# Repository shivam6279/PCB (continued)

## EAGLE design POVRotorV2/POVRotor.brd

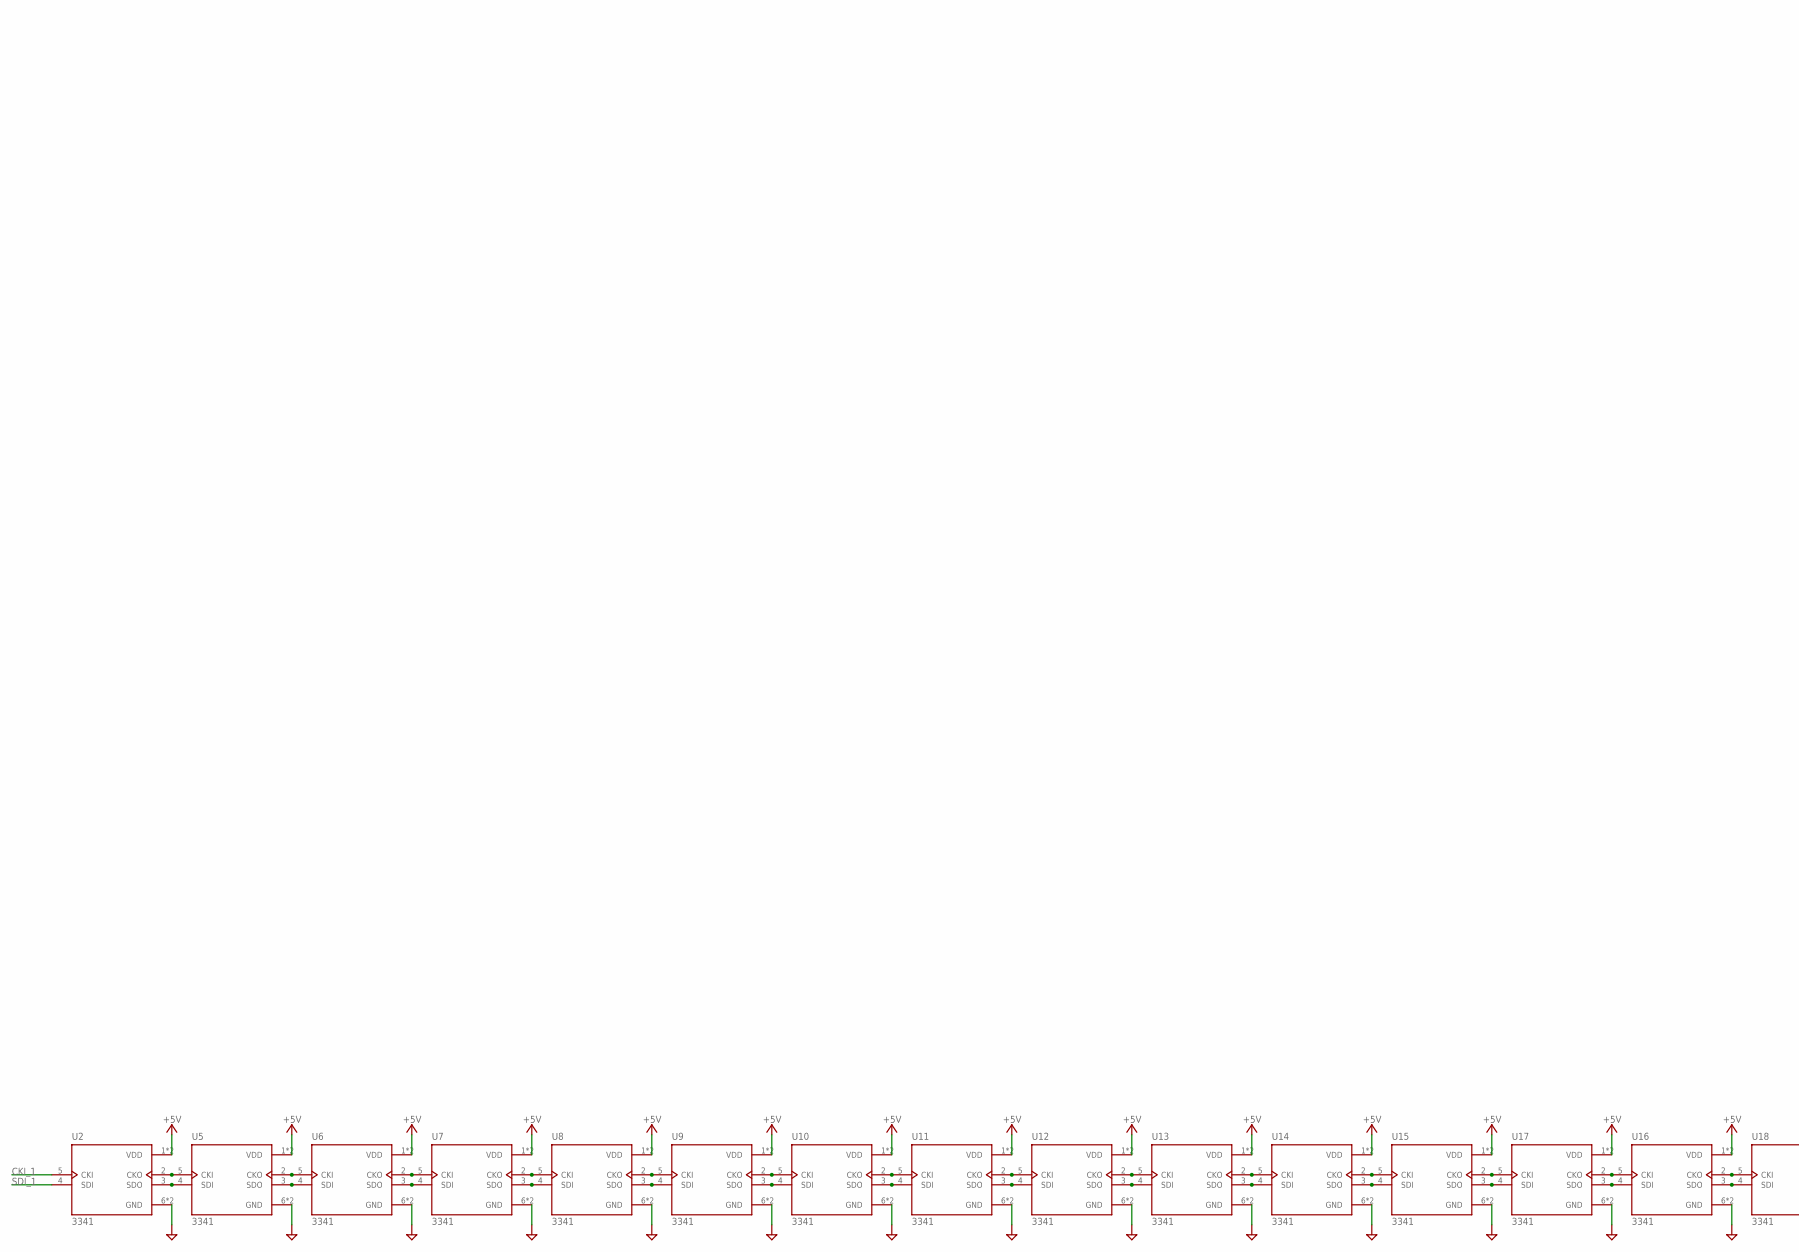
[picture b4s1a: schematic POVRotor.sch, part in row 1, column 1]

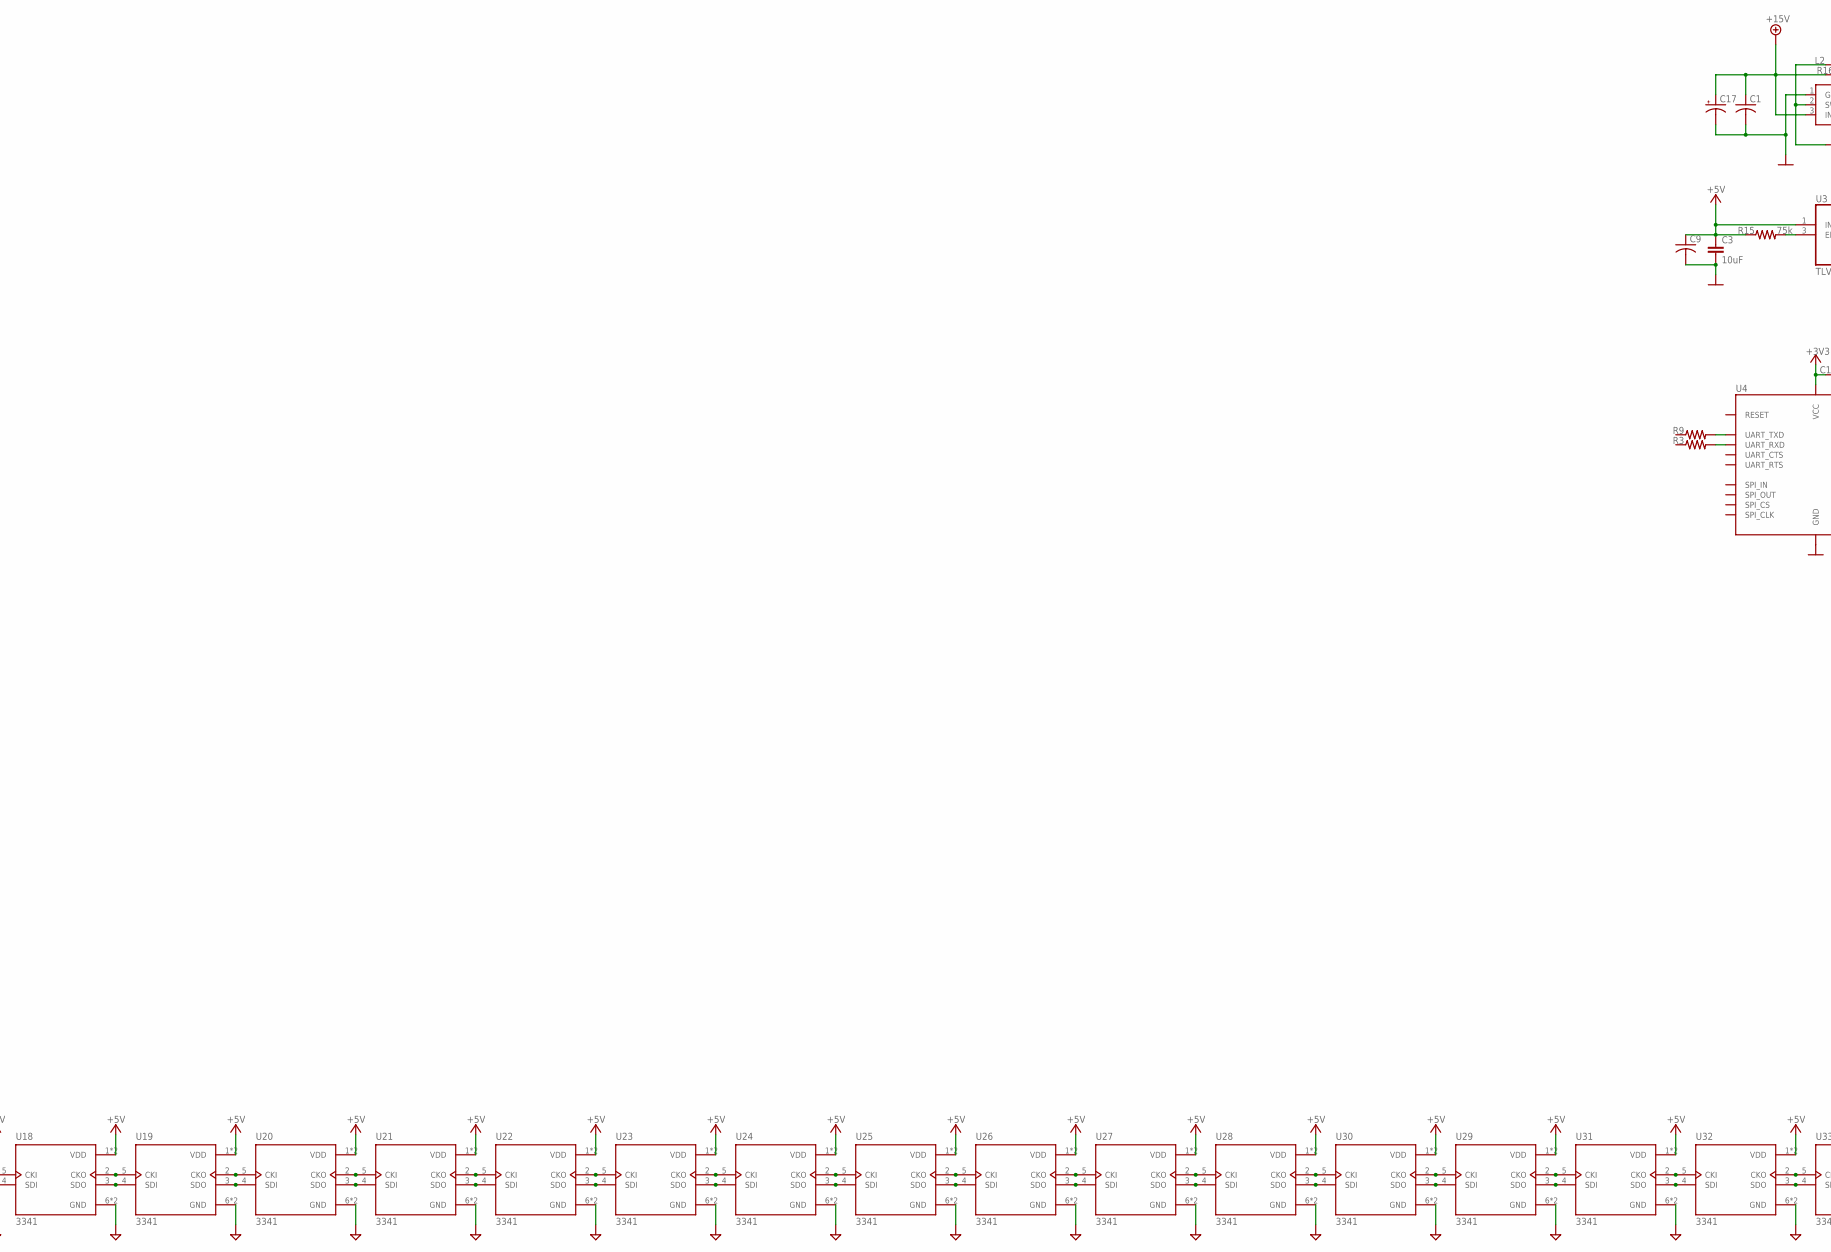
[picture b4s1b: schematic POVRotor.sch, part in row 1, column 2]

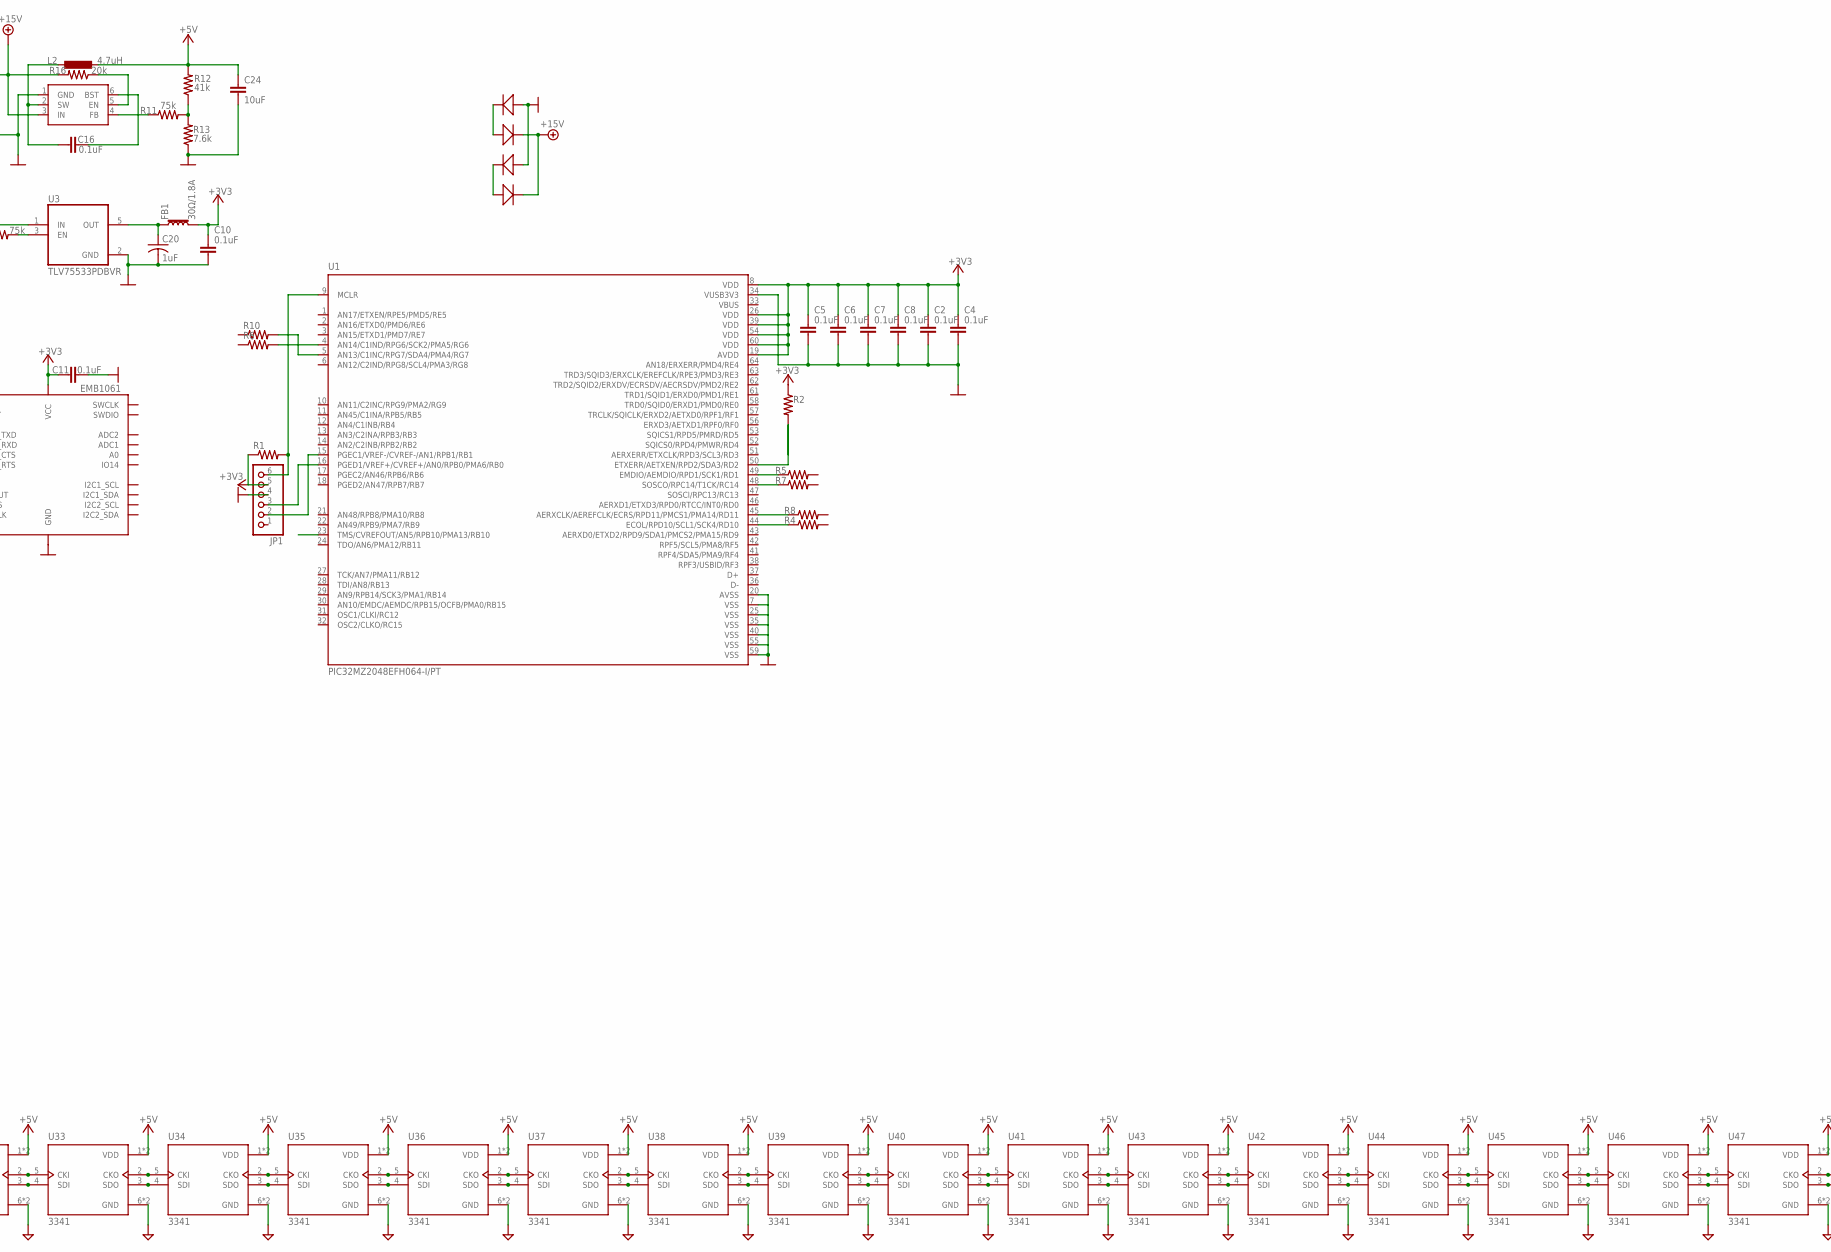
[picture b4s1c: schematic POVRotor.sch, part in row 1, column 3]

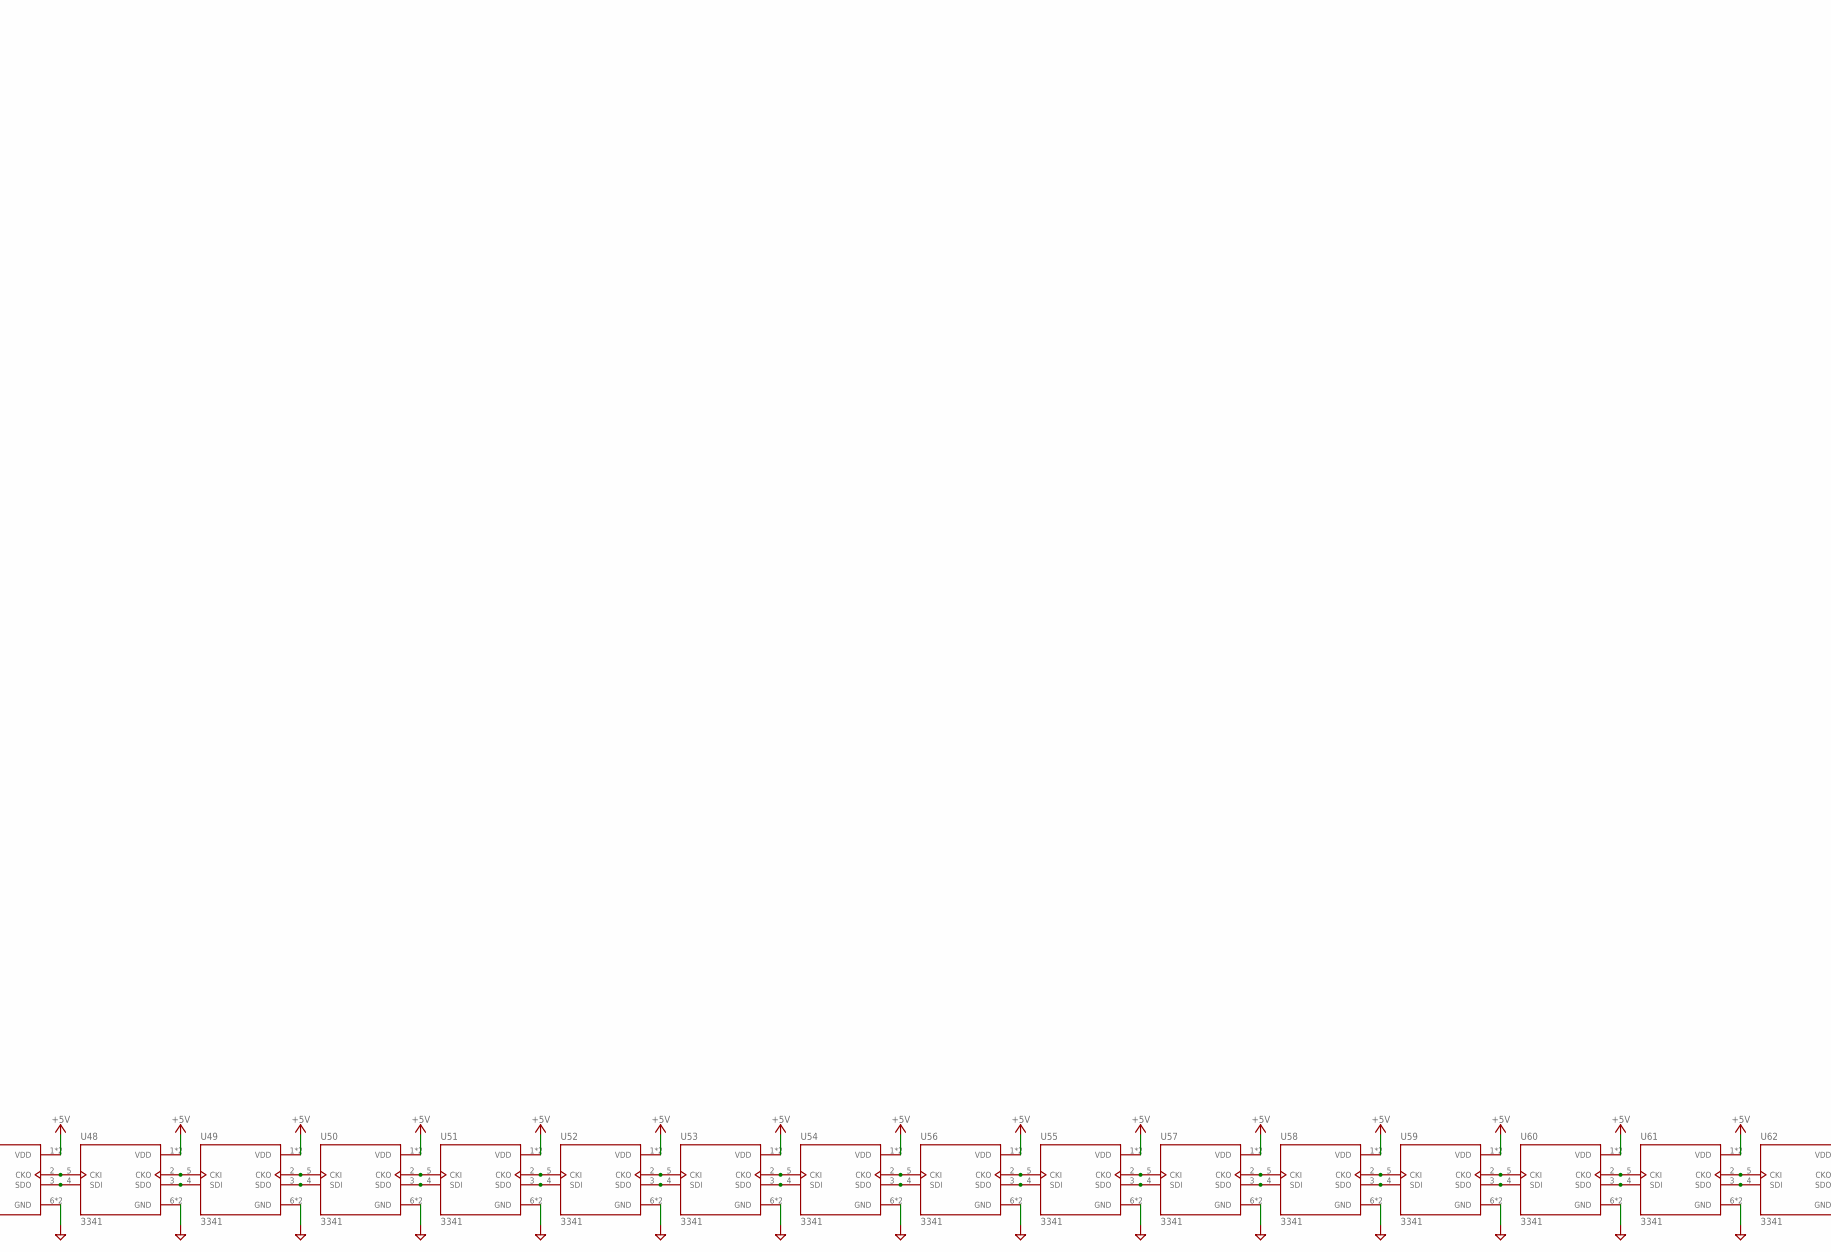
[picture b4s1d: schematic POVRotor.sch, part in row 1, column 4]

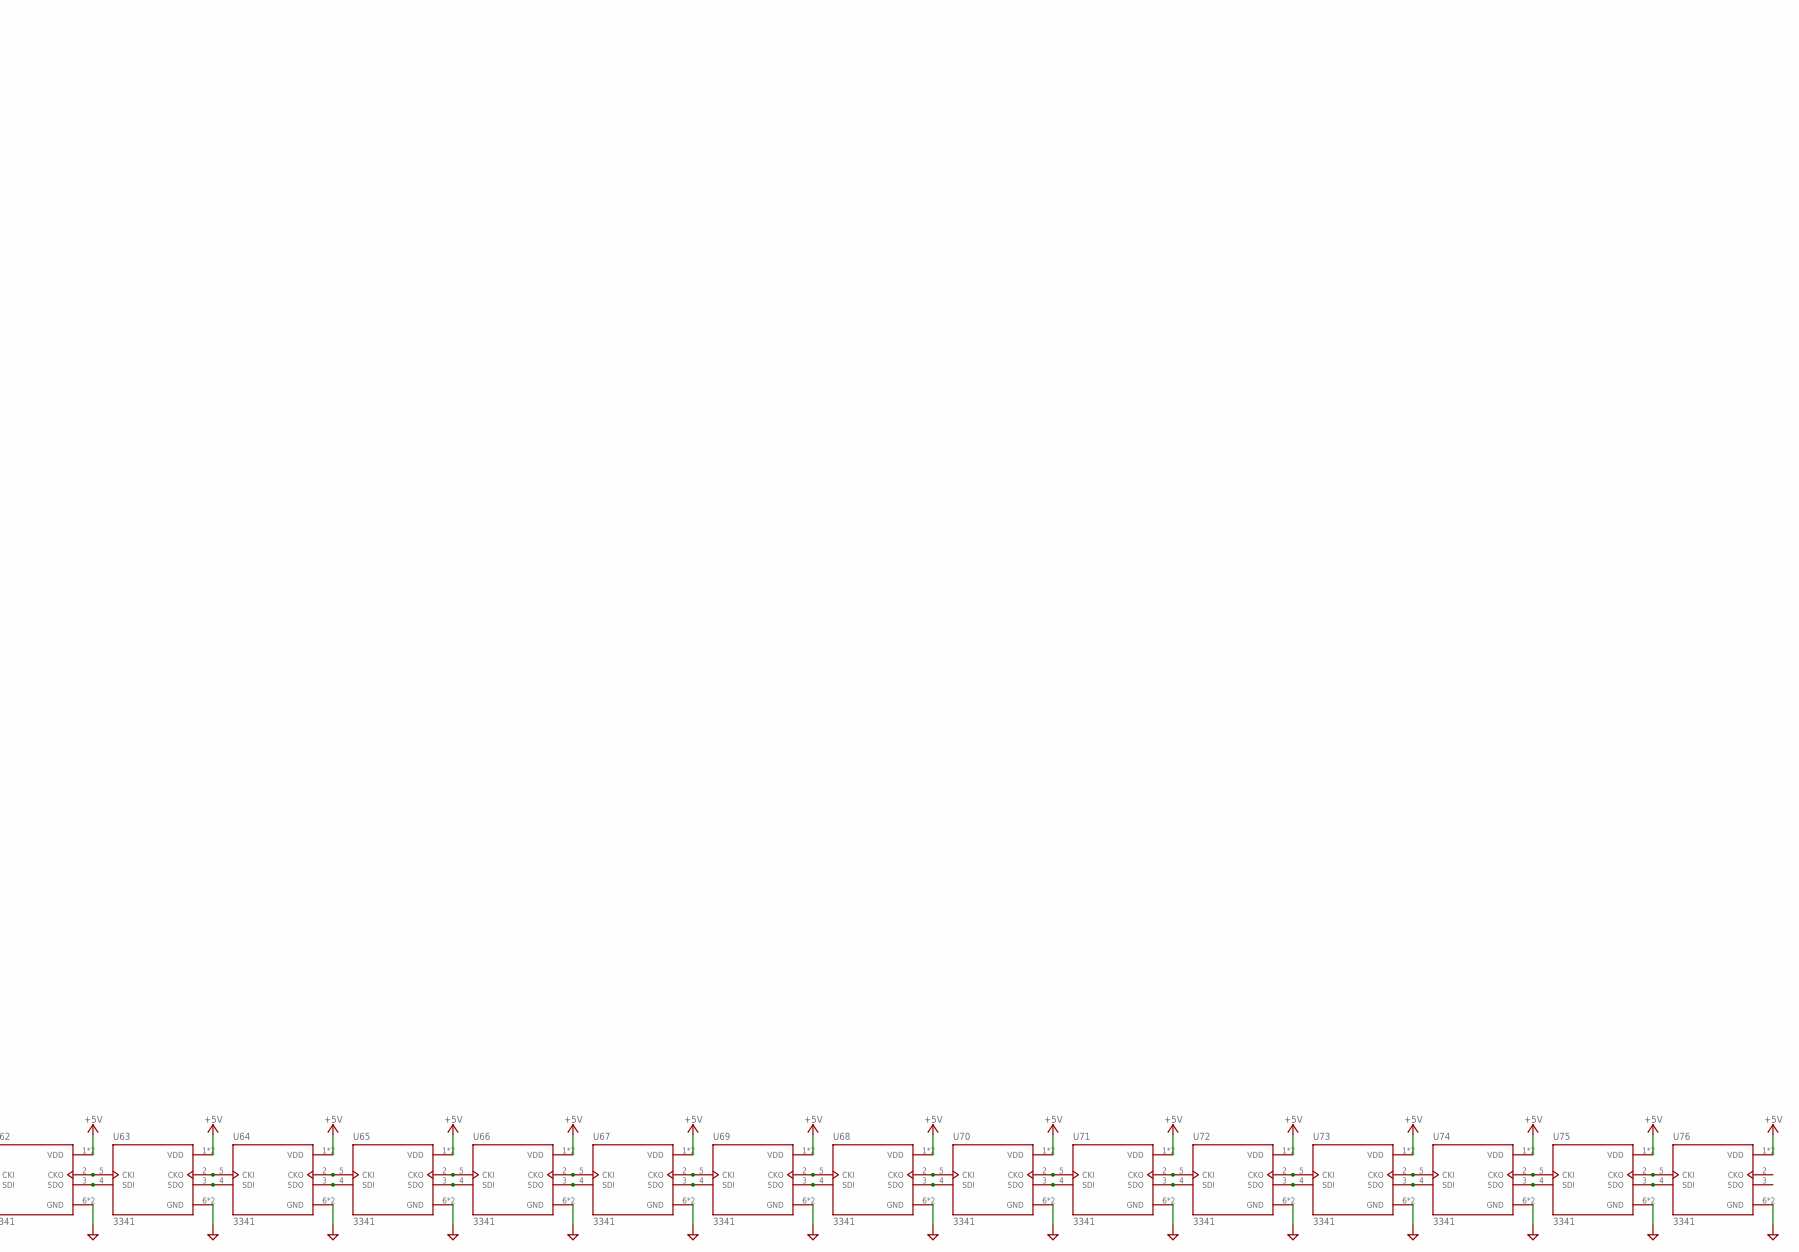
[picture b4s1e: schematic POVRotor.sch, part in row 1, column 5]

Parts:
C1, C9: C-USC0805; C0805
C2, C4, C5, C6, C7, C8, C10, C11, C16: 0.1uF; C0603
C3, C24: 10uF; C1206
C17: CPOL-USC/6032-28R; C/6032-28R
C20: 1uF; C0805
D2, D3, D4, D5: SMD-DIODE-SCHOTTKY-40V-3A(DO-214AB); DO-214AB
FB1: 30Ω/1.8A; 0603
JP1: PINHD-1X6/90; 1X06/90
L2: 4.7uH; L2825P
R1, R2, R3, R4, R5, R6, R7, R8, R9, R10: R-US_R0603; R0603
R11, R15: 75k; R0603
R12: 41k; R0603
R13: 7.6k; R0603
R16: 20k; R0603
U1: PIC32MZ2048EFH064-I/PT; QFP50P1200X1200X120-64N
U2, U5, U6, U7, U8, U9, U10, U11, U12, U13, U14, U15, U16, U17, U18, U19, U20, U21, U22, U23, U24, U25, U26, U27, U28, U29, U30, U31, U32, U33, U34, U35, U36, U37, U38, U39, U40, U41, U42, U43, U44, U45, U46, U47, U48, U49, U50, U51, U52, U53, U54, U55, U56, U57, U58, U59, U60, U61, U62, U63, U64, U65, U66, U67, U68, U69, U70, U71, U72, U73, U74, U75, U76: 3341; LED_3341
U3: TLV75533PDBVR; SOT95P280X145-5N
U4: EMB1061
U$74: AP65211A; SOT95P280X140-6N

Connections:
+5V: C3.1, C9.1, C24.1, L2.1, R12.2, R15.1, U2.1 (VDD), U2.8 (VDD), U3.1 (IN), U5.1 (VDD), U5.8 (VDD), U6.1 (VDD), U6.8 (VDD), U7.1 (VDD), U7.8 (VDD), U8.1 (VDD), U8.8 (VDD), U9.1 (VDD), U9.8 (VDD), U10.1 (VDD), U10.8 (VDD), U11.1 (VDD), U11.8 (VDD), U12.1 (VDD), U12.8 (VDD), U13.1 (VDD), U13.8 (VDD), U14.1 (VDD), U14.8 (VDD), U15.1 (VDD), U15.8 (VDD), U16.1 (VDD), U16.8 (VDD), U17.1 (VDD), U17.8 (VDD), U18.1 (VDD), U18.8 (VDD), U19.1 (VDD), U19.8 (VDD), U20.1 (VDD), U20.8 (VDD), U21.1 (VDD), U21.8 (VDD), U22.1 (VDD), U22.8 (VDD), U23.1 (VDD), U23.8 (VDD), U24.1 (VDD), U24.8 (VDD), U25.1 (VDD), U25.8 (VDD), U26.1 (VDD), U26.8 (VDD), U27.1 (VDD), U27.8 (VDD), U28.1 (VDD), U28.8 (VDD), U29.1 (VDD), U29.8 (VDD), U30.1 (VDD), U30.8 (VDD), U31.1 (VDD), U31.8 (VDD), U32.1 (VDD), U32.8 (VDD), U33.1 (VDD), U33.8 (VDD), U34.1 (VDD), U34.8 (VDD), U35.1 (VDD), U35.8 (VDD), U36.1 (VDD), U36.8 (VDD), U37.1 (VDD), U37.8 (VDD), U38.1 (VDD), U38.8 (VDD), U39.1 (VDD), U39.8 (VDD), U40.1 (VDD), U40.8 (VDD), U41.1 (VDD), U41.8 (VDD), U42.1 (VDD), U42.8 (VDD), U43.1 (VDD), U43.8 (VDD), U44.1 (VDD), U44.8 (VDD), U45.1 (VDD), U45.8 (VDD), U46.1 (VDD), U46.8 (VDD), U47.1 (VDD), U47.8 (VDD), U48.1 (VDD), U48.8 (VDD), U49.1 (VDD), U49.8 (VDD), U50.1 (VDD), U50.8 (VDD), U51.1 (VDD), U51.8 (VDD), U52.1 (VDD), U52.8 (VDD), U53.1 (VDD), U53.8 (VDD), U54.1 (VDD), U54.8 (VDD), U55.1 (VDD), U55.8 (VDD), U56.1 (VDD), U56.8 (VDD), U57.1 (VDD), U57.8 (VDD), U58.1 (VDD), U58.8 (VDD), U59.1 (VDD), U59.8 (VDD), U60.1 (VDD), U60.8 (VDD), U61.1 (VDD), U61.8 (VDD), U62.1 (VDD), U62.8 (VDD), U63.1 (VDD), U63.8 (VDD), U64.1 (VDD), U64.8 (VDD), U65.1 (VDD), U65.8 (VDD), U66.1 (VDD), U66.8 (VDD), U67.1 (VDD), U67.8 (VDD), U68.1 (VDD), U68.8 (VDD), U69.1 (VDD), U69.8 (VDD), U70.1 (VDD), U70.8 (VDD), U71.1 (VDD), U71.8 (VDD), U72.1 (VDD), U72.8 (VDD), U73.1 (VDD), U73.8 (VDD), U74.1 (VDD), U74.8 (VDD), U75.1 (VDD), U75.8 (VDD), U76.1 (VDD), U76.8 (VDD); also elsewhere on the board
+15V: C1.1, C17.+, D2.2 (-), D3.2 (-), R16.2, U$74.3 (IN)
BLE_RX: R3.2, U4.P$11 (UART_RXD)
BLE_TX: R9.2, U4.P$10 (UART_TXD)
CKI_1: R5.2, U2.5 (CKI)
GND: C1.2, C2.2, C3.2, C4.2, C5.2, C6.2, C7.2, C8.2, C9.2, C10.2, C11.2, C17.-, C20.2, C24.2, D4.1 (+), D5.1 (+), JP1.4, R13.1, U1.7 (VSS), U1.20 (AVSS), U1.25 (VSS), U1.34 (VUSB3V3), U1.35 (VSS), U1.40 (VSS), U1.55 (VSS), U1.59 (VSS), U2.6 (GND), U2.7 (GND), U3.2 (GND), U4.P$9 (GND), U4.P$22 (GND), U5.6 (GND), U5.7 (GND), U6.6 (GND), U6.7 (GND), U7.6 (GND), U7.7 (GND), U8.6 (GND), U8.7 (GND), U9.6 (GND), U9.7 (GND), U10.6 (GND), U10.7 (GND), U11.6 (GND), U11.7 (GND), U12.6 (GND), U12.7 (GND), U13.6 (GND), U13.7 (GND), U14.6 (GND), U14.7 (GND), U15.6 (GND), U15.7 (GND), U16.6 (GND), U16.7 (GND), U17.6 (GND), U17.7 (GND), U18.6 (GND), U18.7 (GND), U19.6 (GND), U19.7 (GND), U20.6 (GND), U20.7 (GND), U21.6 (GND), U21.7 (GND), U22.6 (GND), U22.7 (GND), U23.6 (GND), U23.7 (GND), U24.6 (GND), U24.7 (GND), U25.6 (GND), U25.7 (GND), U26.6 (GND), U26.7 (GND), U27.6 (GND), U27.7 (GND), U28.6 (GND), U28.7 (GND), U29.6 (GND), U29.7 (GND), U30.6 (GND), U30.7 (GND), U31.6 (GND), U31.7 (GND), U32.6 (GND), U32.7 (GND), U33.6 (GND), U33.7 (GND), U34.6 (GND), U34.7 (GND), U35.6 (GND), U35.7 (GND), U36.6 (GND), U36.7 (GND), U37.6 (GND), U37.7 (GND), U38.6 (GND), U38.7 (GND), U39.6 (GND), U39.7 (GND), U40.6 (GND), U40.7 (GND), U41.6 (GND), U41.7 (GND), U42.6 (GND), U42.7 (GND), U43.6 (GND), U43.7 (GND), U44.6 (GND), U44.7 (GND), U45.6 (GND), U45.7 (GND), U46.6 (GND), U46.7 (GND), U47.6 (GND), U47.7 (GND), U48.6 (GND), U48.7 (GND), U49.6 (GND), U49.7 (GND), U50.6 (GND), U50.7 (GND), U51.6 (GND), U51.7 (GND), U52.6 (GND), U52.7 (GND), U53.6 (GND), U53.7 (GND), U54.6 (GND), U54.7 (GND), U55.6 (GND), U55.7 (GND), U56.6 (GND), U56.7 (GND), U57.6 (GND), U57.7 (GND), U58.6 (GND), U58.7 (GND), U59.6 (GND), U59.7 (GND), U60.6 (GND), U60.7 (GND), U61.6 (GND), U61.7 (GND), U62.6 (GND), U62.7 (GND), U63.6 (GND), U63.7 (GND), U64.6 (GND), U64.7 (GND), U65.6 (GND), U65.7 (GND), U66.6 (GND), U66.7 (GND), U67.6 (GND), U67.7 (GND), U68.6 (GND), U68.7 (GND), U69.6 (GND), U69.7 (GND), U70.6 (GND), U70.7 (GND), U71.6 (GND), U71.7 (GND), U72.6 (GND), U72.7 (GND), U73.6 (GND), U73.7 (GND), U74.6 (GND), U74.7 (GND), U75.6 (GND), U75.7 (GND), U76.6 (GND), U76.7 (GND), U$74.1 (GND); also elsewhere on the board
unnamed: D2.1 (+), D5.2 (-)
unnamed: D3.1 (+), D4.2 (-)
unnamed: R15.2, U3.3 (EN)
unnamed: R9.1, U1.51 (AERXERR/ETXCLK/RPD3/SCL3/RD3)
unnamed: R4.2, U4.P$3 (RESET)
unnamed: R16.1, U$74.5 (EN)
unnamed: U5.2 (CKO), U6.5 (CKI)
unnamed: U5.3 (SDO), U6.4 (SDI)
unnamed: U2.2 (CKO), U5.5 (CKI)
unnamed: U2.3 (SDO), U5.4 (SDI)
unnamed: U6.2 (CKO), U7.5 (CKI)
unnamed: JP1.3, U1.16 (PGED1/VREF+/CVREF+/AN0/RPB0/PMA6/RB0)
unnamed: JP1.2, U1.15 (PGEC1/VREF-/CVREF-/AN1/RPB1/RB1)
unnamed: JP1.6, R1.2, U1.9 (MCLR)
unnamed: U26.2 (CKO), U27.5 (CKI)
unnamed: U6.3 (SDO), U7.4 (SDI)
unnamed: U7.2 (CKO), U8.5 (CKI)
unnamed: U7.3 (SDO), U8.4 (SDI)
unnamed: U8.2 (CKO), U9.5 (CKI)
unnamed: R6.1, R7.1, U1.48 (SOSCO/RPC14/T1CK/RC14)
unnamed: U8.3 (SDO), U9.4 (SDI)
unnamed: U9.2 (CKO), U10.5 (CKI)
unnamed: U9.3 (SDO), U10.4 (SDI)
unnamed: U10.2 (CKO), U11.5 (CKI)
unnamed: U10.3 (SDO), U11.4 (SDI)
unnamed: U11.2 (CKO), U12.5 (CKI)
unnamed: U11.3 (SDO), U12.4 (SDI)
unnamed: U12.2 (CKO), U13.5 (CKI)
unnamed: U12.3 (SDO), U13.4 (SDI)
unnamed: U13.2 (CKO), U14.5 (CKI)
unnamed: U13.3 (SDO), U14.4 (SDI)
unnamed: U14.2 (CKO), U15.5 (CKI)
unnamed: U14.3 (SDO), U15.4 (SDI)
unnamed: U15.2 (CKO), U17.5 (CKI)
unnamed: U15.3 (SDO), U17.4 (SDI)
unnamed: U16.5 (CKI), U17.2 (CKO)
unnamed: U16.4 (SDI), U17.3 (SDO)
unnamed: U18.2 (CKO), U19.5 (CKI)
unnamed: U18.3 (SDO), U19.4 (SDI)
unnamed: U16.2 (CKO), U18.5 (CKI)
unnamed: R5.1, U1.49 (EMDIO/AEMDIO/RPD1/SCK1/RD1)
unnamed: U16.3 (SDO), U18.4 (SDI)
unnamed: U19.2 (CKO), U20.5 (CKI)
unnamed: U19.3 (SDO), U20.4 (SDI)
unnamed: U20.2 (CKO), U21.5 (CKI)
unnamed: U20.3 (SDO), U21.4 (SDI)
unnamed: U21.2 (CKO), U22.5 (CKI)
unnamed: U21.3 (SDO), U22.4 (SDI)
unnamed: U22.2 (CKO), U23.5 (CKI)
unnamed: U22.3 (SDO), U23.4 (SDI)
unnamed: U23.2 (CKO), U24.5 (CKI)
unnamed: U23.3 (SDO), U24.4 (SDI)
unnamed: U24.2 (CKO), U25.5 (CKI)
unnamed: U24.3 (SDO), U25.4 (SDI)
unnamed: U25.2 (CKO), U26.5 (CKI)
unnamed: U25.3 (SDO), U26.4 (SDI)
unnamed: C20.1, FB1.1, U3.5 (OUT)
unnamed: U26.3 (SDO), U27.4 (SDI)
unnamed: U27.2 (CKO), U28.5 (CKI)
unnamed: U27.3 (SDO), U28.4 (SDI)
unnamed: U28.2 (CKO), U30.5 (CKI)
unnamed: U28.3 (SDO), U30.4 (SDI)
unnamed: U29.5 (CKI), U30.2 (CKO)
unnamed: U29.4 (SDI), U30.3 (SDO)
unnamed: U31.2 (CKO), U32.5 (CKI)
unnamed: U31.3 (SDO), U32.4 (SDI)
unnamed: U29.2 (CKO), U31.5 (CKI)
unnamed: U29.3 (SDO), U31.4 (SDI)
unnamed: U32.2 (CKO), U33.5 (CKI)
unnamed: U32.3 (SDO), U33.4 (SDI)
unnamed: U33.2 (CKO), U34.5 (CKI)
unnamed: U33.3 (SDO), U34.4 (SDI)
unnamed: U34.2 (CKO), U35.5 (CKI)
unnamed: U34.3 (SDO), U35.4 (SDI)
unnamed: U35.2 (CKO), U36.5 (CKI)
unnamed: U35.3 (SDO), U36.4 (SDI)
unnamed: U36.2 (CKO), U37.5 (CKI)
unnamed: U36.3 (SDO), U37.4 (SDI)
unnamed: U37.2 (CKO), U38.5 (CKI)
unnamed: U37.3 (SDO), U38.4 (SDI)
unnamed: U38.2 (CKO), U39.5 (CKI)
unnamed: U38.3 (SDO), U39.4 (SDI)
unnamed: U39.2 (CKO), U40.5 (CKI)
unnamed: U39.3 (SDO), U40.4 (SDI)
unnamed: U40.2 (CKO), U41.5 (CKI)
unnamed: U40.3 (SDO), U41.4 (SDI)
unnamed: U41.2 (CKO), U43.5 (CKI)
unnamed: U41.3 (SDO), U43.4 (SDI)
unnamed: U42.5 (CKI), U43.2 (CKO)
unnamed: U42.4 (SDI), U43.3 (SDO)
unnamed: U44.2 (CKO), U45.5 (CKI)
unnamed: U44.3 (SDO), U45.4 (SDI)
unnamed: U42.2 (CKO), U44.5 (CKI)
unnamed: U42.3 (SDO), U44.4 (SDI)
unnamed: U45.2 (CKO), U46.5 (CKI)
unnamed: U45.3 (SDO), U46.4 (SDI)
unnamed: U46.2 (CKO), U47.5 (CKI)
unnamed: U46.3 (SDO), U47.4 (SDI)
unnamed: U47.2 (CKO), U48.5 (CKI)
unnamed: U47.3 (SDO), U48.4 (SDI)
unnamed: U48.2 (CKO), U49.5 (CKI)
unnamed: U48.3 (SDO), U49.4 (SDI)
unnamed: U49.2 (CKO), U50.5 (CKI)
unnamed: U49.3 (SDO), U50.4 (SDI)
unnamed: U50.2 (CKO), U51.5 (CKI)
unnamed: U50.3 (SDO), U51.4 (SDI)
unnamed: U51.2 (CKO), U52.5 (CKI)
unnamed: U51.3 (SDO), U52.4 (SDI)
unnamed: U52.2 (CKO), U53.5 (CKI)
unnamed: U52.3 (SDO), U53.4 (SDI)
unnamed: U53.2 (CKO), U54.5 (CKI)
unnamed: U53.3 (SDO), U54.4 (SDI)
unnamed: U54.2 (CKO), U56.5 (CKI)
unnamed: U54.3 (SDO), U56.4 (SDI)
unnamed: U55.5 (CKI), U56.2 (CKO)
unnamed: U55.4 (SDI), U56.3 (SDO)
unnamed: U57.2 (CKO), U58.5 (CKI)
unnamed: U57.3 (SDO), U58.4 (SDI)
unnamed: U55.2 (CKO), U57.5 (CKI)
unnamed: U55.3 (SDO), U57.4 (SDI)
unnamed: U58.2 (CKO), U59.5 (CKI)
unnamed: C16.1, L2.2, U$74.2 (SW)
unnamed: C16.2, U$74.6 (BST)
unnamed: U58.3 (SDO), U59.4 (SDI)
unnamed: U59.2 (CKO), U60.5 (CKI)
unnamed: U59.3 (SDO), U60.4 (SDI)
unnamed: U60.2 (CKO), U61.5 (CKI)
unnamed: U60.3 (SDO), U61.4 (SDI)
unnamed: U61.2 (CKO), U62.5 (CKI)
unnamed: U61.3 (SDO), U62.4 (SDI)
unnamed: U62.2 (CKO), U63.5 (CKI)
unnamed: U62.3 (SDO), U63.4 (SDI)
unnamed: U63.2 (CKO), U64.5 (CKI)
unnamed: U63.3 (SDO), U64.4 (SDI)
unnamed: U64.2 (CKO), U65.5 (CKI)
unnamed: U64.3 (SDO), U65.4 (SDI)
unnamed: U65.2 (CKO), U66.5 (CKI)
unnamed: U65.3 (SDO), U66.4 (SDI)
unnamed: U66.2 (CKO), U67.5 (CKI)
unnamed: U66.3 (SDO), U67.4 (SDI)
unnamed: U67.2 (CKO), U69.5 (CKI)
unnamed: U67.3 (SDO), U69.4 (SDI)
unnamed: U68.5 (CKI), U69.2 (CKO)
unnamed: U68.4 (SDI), U69.3 (SDO)
unnamed: U70.2 (CKO), U71.5 (CKI)
unnamed: U70.3 (SDO), U71.4 (SDI)
unnamed: U68.2 (CKO), U70.5 (CKI)
unnamed: U68.3 (SDO), U70.4 (SDI)
unnamed: U71.2 (CKO), U72.5 (CKI)
unnamed: U71.3 (SDO), U72.4 (SDI)
unnamed: U72.2 (CKO), U73.5 (CKI)
unnamed: U72.3 (SDO), U73.4 (SDI)
unnamed: U73.2 (CKO), U74.5 (CKI)
unnamed: U73.3 (SDO), U74.4 (SDI)
unnamed: U74.2 (CKO), U75.5 (CKI)
unnamed: U74.3 (SDO), U75.4 (SDI)
unnamed: U75.2 (CKO), U76.5 (CKI)
unnamed: U75.3 (SDO), U76.4 (SDI)
unnamed: R11.1, U$74.4 (FB)
unnamed: R11.2, R12.1, R13.2
unnamed: R8.1, U1.45 (AERXCLK/AEREFCLK/ECRS/RPD11/PMCS1/PMA14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)
unnamed: R10.2, U1.5 (AN13/C1INC/RPG7/SDA4/PMA4/RG7)
VBUS: U1.33 (VBUS)

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
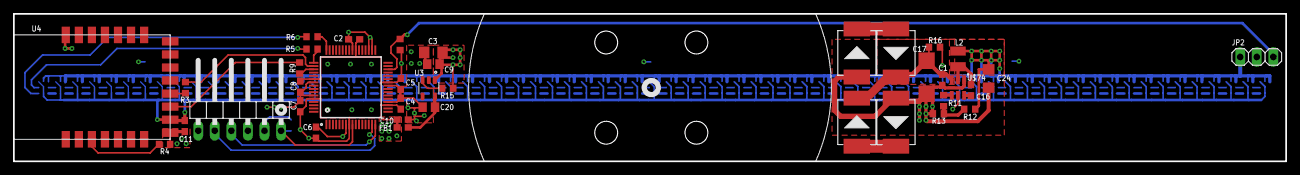
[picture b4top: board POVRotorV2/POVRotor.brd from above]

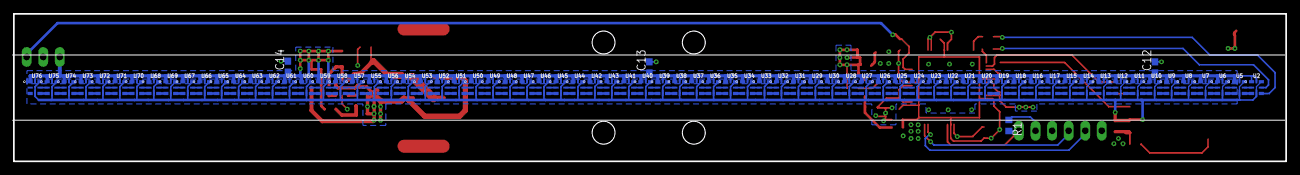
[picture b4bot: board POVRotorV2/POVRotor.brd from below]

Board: 4 copper layers, 195.0 x 22.6 mm, 115 parts (77 on the bottom side), 170 nets.

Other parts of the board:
C12, C13, C14: 0.1uF; C0603
JP2: 1X03

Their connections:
+5V: C12.1, C13.1, C14.1, JP2.1; also elsewhere on the board
GND: C12.2, C13.2, C14.2, JP2.2; also elsewhere on the board

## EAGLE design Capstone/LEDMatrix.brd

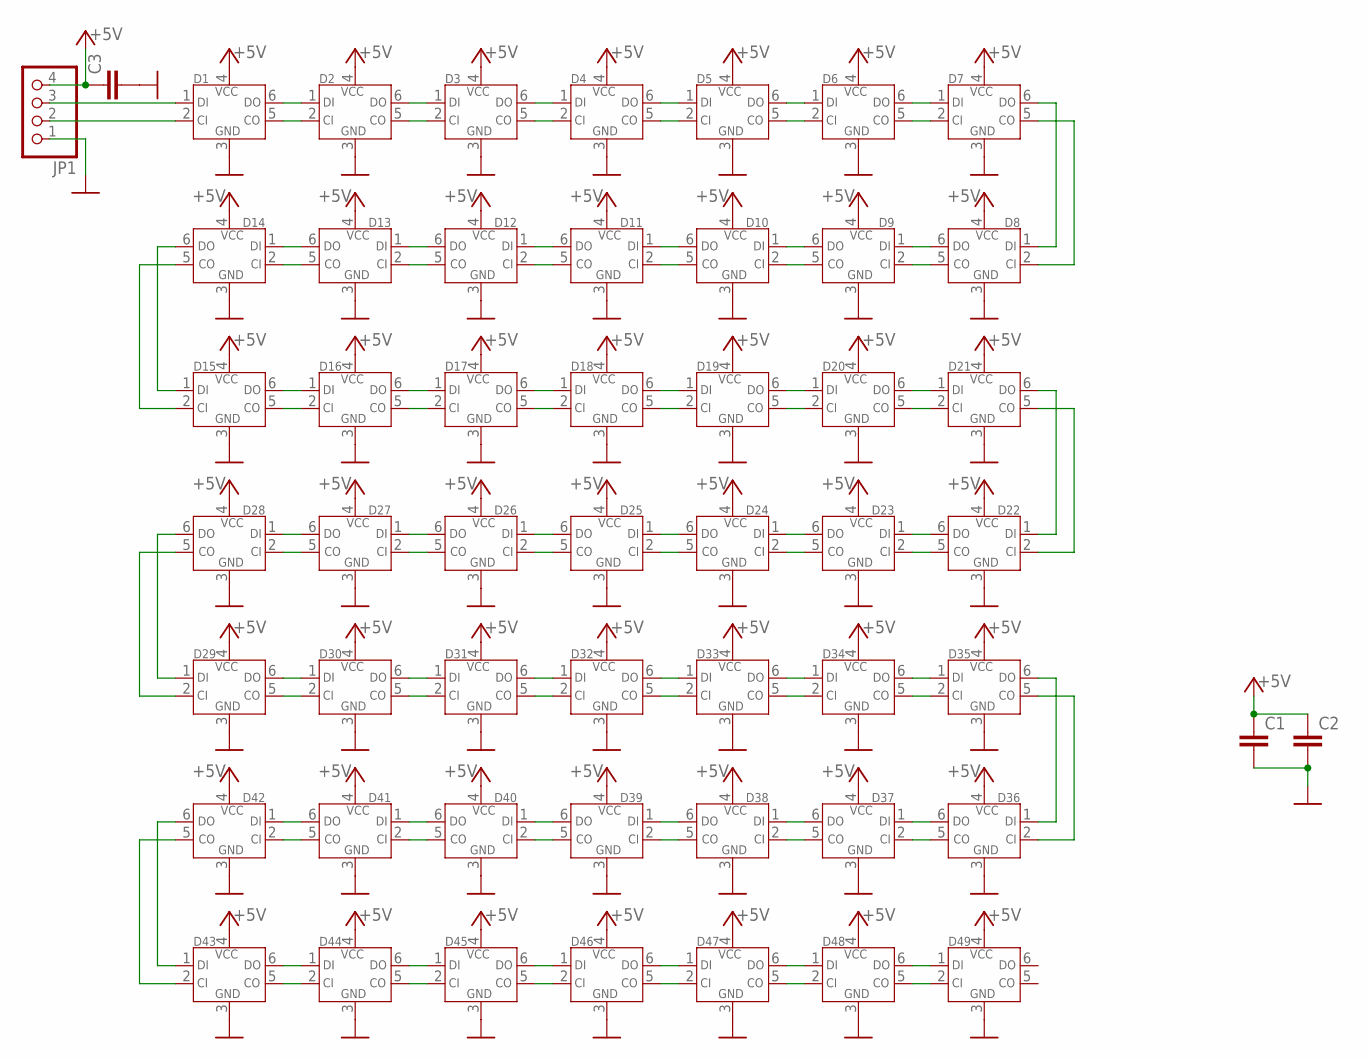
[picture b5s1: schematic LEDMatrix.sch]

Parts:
C1, C2, C3: C-EUC0805; C0805
D1, D2, D3, D4, D5, D6, D7, D8, D9, D10, D11, D12, D13, D14, D15, D16, D17, D18, D19, D20, D21, D22, D23, D24, D25, D26, D27, D28, D29, D30, D31, D32, D33, D34, D35, D36, D37, D38, D39, D40, D41, D42, D43, D44, D45, D46, D47, D48, D49: QBLP679E-RGB; LED_QBLP679E-RGB
JP1: PINHD-1X4; 1X04

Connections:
+5V: C1.1, C2.1, C3.1, D1.4 (VCC), D2.4 (VCC), D3.4 (VCC), D4.4 (VCC), D5.4 (VCC), D6.4 (VCC), D7.4 (VCC), D8.4 (VCC), D9.4 (VCC), D10.4 (VCC), D11.4 (VCC), D12.4 (VCC), D13.4 (VCC), D14.4 (VCC), D15.4 (VCC), D16.4 (VCC), D17.4 (VCC), D18.4 (VCC), D19.4 (VCC), D20.4 (VCC), D21.4 (VCC), D22.4 (VCC), D23.4 (VCC), D24.4 (VCC), D25.4 (VCC), D26.4 (VCC), D27.4 (VCC), D28.4 (VCC), D29.4 (VCC), D30.4 (VCC), D31.4 (VCC), D32.4 (VCC), D33.4 (VCC), D34.4 (VCC), D35.4 (VCC), D36.4 (VCC), D37.4 (VCC), D38.4 (VCC), D39.4 (VCC), D40.4 (VCC), D41.4 (VCC), D42.4 (VCC), D43.4 (VCC), D44.4 (VCC), D45.4 (VCC), D46.4 (VCC), D47.4 (VCC), D48.4 (VCC), D49.4 (VCC), JP1.4
GND: C1.2, C2.2, C3.2, D1.3 (GND), D2.3 (GND), D3.3 (GND), D4.3 (GND), D5.3 (GND), D6.3 (GND), D7.3 (GND), D8.3 (GND), D9.3 (GND), D10.3 (GND), D11.3 (GND), D12.3 (GND), D13.3 (GND), D14.3 (GND), D15.3 (GND), D16.3 (GND), D17.3 (GND), D18.3 (GND), D19.3 (GND), D20.3 (GND), D21.3 (GND), D22.3 (GND), D23.3 (GND), D24.3 (GND), D25.3 (GND), D26.3 (GND), D27.3 (GND), D28.3 (GND), D29.3 (GND), D30.3 (GND), D31.3 (GND), D32.3 (GND), D33.3 (GND), D34.3 (GND), D35.3 (GND), D36.3 (GND), D37.3 (GND), D38.3 (GND), D39.3 (GND), D40.3 (GND), D41.3 (GND), D42.3 (GND), D43.3 (GND), D44.3 (GND), D45.3 (GND), D46.3 (GND), D47.3 (GND), D48.3 (GND), D49.3 (GND), JP1.1
unnamed: D1.6 (DO), D2.1 (DI)
unnamed: D1.5 (CO), D2.2 (CI)
unnamed: D2.6 (DO), D3.1 (DI)
unnamed: D2.5 (CO), D3.2 (CI)
unnamed: D3.6 (DO), D4.1 (DI)
unnamed: D3.5 (CO), D4.2 (CI)
unnamed: D4.6 (DO), D5.1 (DI)
unnamed: D4.5 (CO), D5.2 (CI)
unnamed: D5.6 (DO), D6.1 (DI)
unnamed: D5.5 (CO), D6.2 (CI)
unnamed: D6.6 (DO), D7.1 (DI)
unnamed: D6.5 (CO), D7.2 (CI)
unnamed: D8.6 (DO), D9.1 (DI)
unnamed: D8.5 (CO), D9.2 (CI)
unnamed: D9.6 (DO), D10.1 (DI)
unnamed: D9.5 (CO), D10.2 (CI)
unnamed: D10.6 (DO), D11.1 (DI)
unnamed: D10.5 (CO), D11.2 (CI)
unnamed: D11.6 (DO), D12.1 (DI)
unnamed: D11.5 (CO), D12.2 (CI)
unnamed: D12.6 (DO), D13.1 (DI)
unnamed: D12.5 (CO), D13.2 (CI)
unnamed: D13.6 (DO), D14.1 (DI)
unnamed: D13.5 (CO), D14.2 (CI)
unnamed: D7.6 (DO), D8.1 (DI)
unnamed: D7.5 (CO), D8.2 (CI)
unnamed: D15.6 (DO), D16.1 (DI)
unnamed: D15.5 (CO), D16.2 (CI)
unnamed: D16.6 (DO), D17.1 (DI)
unnamed: D16.5 (CO), D17.2 (CI)
unnamed: D17.6 (DO), D18.1 (DI)
unnamed: D17.5 (CO), D18.2 (CI)
unnamed: D18.6 (DO), D19.1 (DI)
unnamed: D18.5 (CO), D19.2 (CI)
unnamed: D19.6 (DO), D20.1 (DI)
unnamed: D19.5 (CO), D20.2 (CI)
unnamed: D20.6 (DO), D21.1 (DI)
unnamed: D20.5 (CO), D21.2 (CI)
unnamed: D22.6 (DO), D23.1 (DI)
unnamed: D22.5 (CO), D23.2 (CI)
unnamed: D23.6 (DO), D24.1 (DI)
unnamed: D23.5 (CO), D24.2 (CI)
unnamed: D24.6 (DO), D25.1 (DI)
unnamed: D24.5 (CO), D25.2 (CI)
unnamed: D25.6 (DO), D26.1 (DI)
unnamed: D25.5 (CO), D26.2 (CI)
unnamed: D26.6 (DO), D27.1 (DI)
unnamed: D26.5 (CO), D27.2 (CI)
unnamed: D27.6 (DO), D28.1 (DI)
unnamed: D27.5 (CO), D28.2 (CI)
unnamed: D21.6 (DO), D22.1 (DI)
unnamed: D21.5 (CO), D22.2 (CI)
unnamed: D29.6 (DO), D30.1 (DI)
unnamed: D29.5 (CO), D30.2 (CI)
unnamed: D30.6 (DO), D31.1 (DI)
unnamed: D30.5 (CO), D31.2 (CI)
unnamed: D31.6 (DO), D32.1 (DI)
unnamed: D31.5 (CO), D32.2 (CI)
unnamed: D32.6 (DO), D33.1 (DI)
unnamed: D32.5 (CO), D33.2 (CI)
unnamed: D33.6 (DO), D34.1 (DI)
unnamed: D33.5 (CO), D34.2 (CI)
unnamed: D34.6 (DO), D35.1 (DI)
unnamed: D34.5 (CO), D35.2 (CI)
unnamed: D36.6 (DO), D37.1 (DI)
unnamed: D36.5 (CO), D37.2 (CI)
unnamed: D37.6 (DO), D38.1 (DI)
unnamed: D37.5 (CO), D38.2 (CI)
unnamed: D38.6 (DO), D39.1 (DI)
unnamed: D38.5 (CO), D39.2 (CI)
unnamed: D39.6 (DO), D40.1 (DI)
unnamed: D39.5 (CO), D40.2 (CI)
unnamed: D40.6 (DO), D41.1 (DI)
unnamed: D40.5 (CO), D41.2 (CI)
unnamed: D41.6 (DO), D42.1 (DI)
unnamed: D41.5 (CO), D42.2 (CI)
unnamed: D35.6 (DO), D36.1 (DI)
unnamed: D35.5 (CO), D36.2 (CI)
unnamed: D14.6 (DO), D15.1 (DI)
unnamed: D14.5 (CO), D15.2 (CI)
unnamed: D28.6 (DO), D29.1 (DI)
unnamed: D28.5 (CO), D29.2 (CI)
unnamed: D43.6 (DO), D44.1 (DI)
unnamed: D43.5 (CO), D44.2 (CI)
unnamed: D44.6 (DO), D45.1 (DI)
unnamed: D44.5 (CO), D45.2 (CI)
unnamed: D45.6 (DO), D46.1 (DI)
unnamed: D45.5 (CO), D46.2 (CI)
unnamed: D46.6 (DO), D47.1 (DI)
unnamed: D46.5 (CO), D47.2 (CI)
unnamed: D47.6 (DO), D48.1 (DI)
unnamed: D47.5 (CO), D48.2 (CI)
unnamed: D48.6 (DO), D49.1 (DI)
unnamed: D48.5 (CO), D49.2 (CI)
unnamed: D1.1 (DI), JP1.3
unnamed: D1.2 (CI), JP1.2
unnamed: D42.6 (DO), D43.1 (DI)
unnamed: D42.5 (CO), D43.2 (CI)
